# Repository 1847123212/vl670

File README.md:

VL670/VL671 Development Board - USB 2.0 to 3.0 Transaction Translator
======================================================================

### Revision

This is version v0.02b (git branch usb-b), which removes the USB Type-C
connector due to chip shortage.

The v0.02 design with the original USB Type-C connector is
[here](https://notabug.org/niconiconi/vl670/src/main)

The original v0.01 design is obsolete, but it's still
[available here](https://notabug.org/niconiconi/vl670/src/v0.01).

### Introduction

#### The Problem

From a technical standpoint, USB 3.0 SuperSpeed (5 Gbps) is not an
upgrade to the existing USB 2.0 High-Speed (480 Mbps) standard,
instead, USB 3.0 is a completely new system of its own, which
operates independently from USB 2.0. Both the physical and protocol
layer have major differences. Backward compatibility is only maintained
by mandating all USB 3.0 devices to include a separate set of legacy
USB 2.0 controllers, transceivers, and wirings.

Because a USB 3.0 port is really a USB 3.0 and USB 2.0 port slapped
together, it creates some limitations.

* Bandwidth: You may want to simutaneously access multiple USB 2.0
devices, such as many USB flash drives, video cameras, or Software
Defined Radios (SDR) over a single USB 3.0 port using a USB hub,
since it has 5 Gbps bandwidth. However, you cannot do this - the total
bandwidth of all USB 2.0 devices is still limited to 480 Mbps, just
like a regular USB 2.0 port.

* Signal Extension and Isolation: Counter-intuitively, it's easier to
transmit USB 3.0 signals (not USB 2.0 High-Speed) over long distances,
or to galvanically isolate them. Its physical layer is actually simpler
than USB 2.0 - it uses two pairs of unidirectional, 8b/10b encoded,
differential signals. This type of signal is commonly found in almost
all high-speed digital systems, many standard hardware interfaces and
transceivers exist. On the other hand, USB 2.0 signaling is its own
design, its half-duplex nature further complicates the implementation.
Thus, in some non-standard custom systems, only a USB 3.0 link is
physically available.

For home and office users, both limitations may not be a problem,
but for hardware developers and experimenters who work with custom
systems, this can be problematic.

#### VL670/VL671 Transaction Translator

The VL670/671 is a specialized ASIC developed by VIA Labs, Inc., it's a USB
2.0 to USB 3.0 *transaction translator*, in other words, it translates the
legacy USB 2.0 traffic and transparently upgrades the device to an USB 3.0
SuperSpeed device by emulation, enabling a legacy USB 2.0 device to make use
of USB 3.0. By transparently upgrading a legacy USB 2.0 device to an emulated
USB 3.0 device, both problems are eliminated.

This is not a perfect solution, first, it's technically a violation of the
USB standards, also device compatibility is limited. Nevertheless, it's
still helpful to hardware developers and can solve many practical problems
in hardware Research and Development.

This technology is marketed as "SuperTT" (Super Transaction Translator)
by some OEM vendors.

#### My Project

Due to the specialized nature of the VL670/VL671 ASIC, it's almost unheard of
by most developers.

This project is an effort to create a free and open source hardware design of a
development board for the VL670/VL671 ASIC, to facilitate hardware evaluation and
experiments by other community developers, hopefully to help solving your USB
problems in your custom systems.

This development board is intended solely for hardware or software developers for
use in a research and development setting to facilitate evaluation, experimentation,
or technical analysis. It's not designed for consumer use, and it also should not be
used as a part or subassembly in any finished product.

#### Generations

VL670 is already obsolete. The second generation is VL671. This development board
supports both VL670 and VL671, and the use of VL671 is strongly recommended (though
not without its own problems).

Both chips are highly compatibile, the only modification needed is a single LED
output.  If VL670 is used, solder resistor `R9`, otherwise, solder resistor `R13`.

### Usage

#### LED Status

##### D2

* On: A USB 2.0 device has just connected and its traffic is being translated
to USB 3.0 traffic by VL67x (*VL670 only, not on VL671: or the processor is being
held in reset by the SPI header*).

* Off: A USB 3.0 or 2.0 device is connected and its traffic is passing
through VL670 as-is without any translation.

* Blink: Initial power-on reset, or a USB 2.0 device has just connected (*VL670
only, not on VL671*).

##### D20

* On: The power rail `+5V_SW` for downstream USB-A port is switched on.
Normally, this LED should be always on.

* Off: The power rail `+5V_SW` for downstream USB-A port is switched off.
This indicates the power supply circuit is malfunctional. First, check the
`5V` input, and whether the downstream USB port has a short circuit. Then,
check the USB power switch chip `U4` and pull-down resistor R15.

#### Voltage Level

All I/O are 3.3 V LVCMOS. Applying 5 V TTL level can damage the VL670,
its SPI flash, or both.

Before reading or writing to the Flash via SPI, the 5V power must also be
applied via the USB cable or the pin header. Attempting to program the SPI
Flash with an external programming without applying 5V power can damage
components.

#### SPI header

An SPI pin header is located at the top right of the board. By default, it's
connected directly to both the VL670 controller and its SPI Flash, allowing
one to probe the SPI bus while the controller is running. In this default mode,
applying voltages to the SPI header is prohibited, otherwise damage may occur.

To read or write the Flash via SPI, the `/EN` (a.k.a `ISP_ENABLE`) pin of the pin
header is grounded (by bridging pin 6 and 7 on the pin header), the processor is
cut off from the SPI bus and held in reset, giving the SPI pin header exclusive
access to the Flash.

For more information, see *Theory of Operation*, section *SPI Debugging and
Programming* and schematics.

#### GPIO header

All GPIO pin header is located at the top left of the board, exposing all
GPIOs of VL67x. Nevertheless, their functionality is unclear and it's
only useful for reverse engineering.

For more information, see *Theory of Operation*, section *Oddities* and
schematics.

### Known Issues

#### Limitations

1. If the USB-C cable is inserted very slowly, USB 3.0 fails, only USB 2.0
is detected, thus forcing the chip to enter USB 2.0 passthrough mode. This
is working by design and it's not a bug, however, it may cause misleading
or confusing behaviors, thus, `R1` and `R2` are removed by default, forcing
VL67x to always work in transaction translator mode.

2. In VL670, USB 3.0 passthrough is not reliable and it's not compatible
with some devices, this is a VL670 limitation. In VL671, USB 3.0 passthrough
is almost completely broken due to firmware limitation, the only compatible
device is a USB 3 Hub, direct attachment of a USB 3 device is not compatible.
Also, because the USB 3 signal path is doubled in passthrough mode, any cable
longer than 50 centimeters may cause enumeration failures. Thus, USB 3.0
passthrough mode should be avoided. If you want to test a combo USB 2/3 device,
I recommend using a pure USB 2.0 hub to completely isolate the USB 3 signals.

    * If you ever need to test USB 3.0 passthrough mode, you should always
    use a short USB-C cable, no longer than 50 centimeters to minimize signal
    loss. The ideal setup for USB 3 passthrough testing is: Host, 50 centimeter
    USB cable, VL671, very short USB cable, USB 3 Hub, device. Failure to follow
    it to cause enumeration and other failures. For USB 2 transaction mode, no
    special precaution is needed.

    * A hybrid VL670 w/ USB hub topology can be used to work around the
    problem, it's briefly in the next section of the document. USB redrivers
    and retimers can also solve the hardware problem (but not the firmware
    bug). Since USB 3 passthrough is already broken enough and adding either
    solution makes the project more complicated, I choose not to do it.

3. The upstream and downstream USB ports have no common-mode chokes for
the signals. Electromagnetic compatibility performance is limited. This
is an intentional decision, since adding them reduces the USB 3 link
budget needed for the already problematic USB 3 passthrough mode.

4. Not all devices are supported by the transaction translator. Sometimes
the incompatibility is a hardware or protocol limitation, other times it
can be a driver problem - many drivers make certain assumptions of the USB
device, which may no longer be true after the device is emulated by VL670
as a SuperSpeed device.

    * USB Attached SCSI (UAS) doesn't work in transaction translator mode.
    But it can be disabled at the device driver of the operating system.

### Photos

#### Front and Back of the PCB

### Schematics

* [PDF schematics](https://notabug.org/niconiconi/vl670/raw/usb-b/schematics/vl670-schematics.pdf)

* [PDF layout](https://notabug.org/niconiconi/vl670/raw/usb-b/schematics/vl670-layout.pdf)

### BOM

* [Bill of Material](https://notabug.org/niconiconi/vl670/src/usb-b/bom)

### Datasheets

Datasheets for all components on the development board can be found at GitLab.

* [Datasheets Repository](https://gitlab.com/niconicon1/vl670-datasheets)

It contains the following documents.

* [VL670 USB2.0 to USB3.0 Transaction Translator](https://gitlab.com/niconicon1/vl670-datasheets/-/raw/main/DS_VL670_115.pdf)

* [VL671 Low Power USB 2.0 to USB 3.1 Gen1 Transaction Translator](https://gitlab.com/niconicon1/vl670-datasheets/-/raw/main/DS_VL671_080.PDF)

* [HD3SS3220 USB Type-C DRP Port Controller with SuperSpeed 2:1 MUX](https://gitlab.com/niconicon1/vl670-datasheets/-/raw/main/hd3ss3220.pdf)

* [TPS20xxC and TPS20xxC-2 Current Limited, Power-Distribution Switches](https://gitlab.com/niconicon1/vl670-datasheets/-/raw/main/tps2061c.pdf)

* [GD25D10C/05C 3.3V Uniform Sector Standard and Dual Serial Flash](https://gitlab.com/niconicon1/vl670-datasheets/-/raw/main/GD25D05C.pdf)

* [SN74LVC2G66 Dual Bilateral Analog Switch](https://gitlab.com/niconicon1/vl670-datasheets/-/raw/main/sn74lvc2g66.pdf)

* [ESD7104 Low Capacitance ESD Protection Diode for High Speed Data Line](https://gitlab.com/niconicon1/vl670-datasheets/-/raw/main/ESD7104-D.PDF)

* [ESD5B5.0ST1G-N ESD Protection Diode](https://gitlab.com/niconicon1/vl670-datasheets/-/raw/main/ESD5B5.0ST1G-N.pdf)

### Firmware

The firmware for the SPI Flash can be found at GitLab. Both VL670 and VL671
firmware files are included.

* [SPI Flash Firmware](https://gitlab.com/niconicon1/vl670-firmware)

#### Non-Free

Unfortunately, VL670/671 is driven by a microcontroller and requires a
proprietary firmware to operate.

Nevertheless, the firmware is burned into the Flash memory only once after
the device is assembled, and it's fetched by the VL670 ASIC itself, not
uploaded from a user's host computer, nor it executes any code on a user's
host computer or operating system. If we make the firmware read-only and
unmodifiable by pure software, the firmware effectively "vanishes" from the
software domain and becomes a part of the hardware itself, making the hardware
qualifies as free device, just like [how OpenMoko did it](https://lwn.net/Articles/460654/).
Another benefit is improved security, as malicious software is unable to
reprogram the firmware via USB to launch a BadUSB attack.

This is implemented as jumper `JP1`, once the jumper is hardwired on the board,
the Flash is read-only and cannot be modified by software without hardware
modifications.

That being said, this is a somewhat "underhanded" way to bypass the free software
and hardware requirements and this behavior stays exactly at the borderline of
the definition of "free", just moving one more nanometer away makes it non-free.
This is hardly satisfactory! But this is all we have at the current moment.

#### Reverse Engineering

The long term solution is reverse engineering the firmware and writing a free and
open reimplementation. This also enables us to customize the firmware for our
needs, fixing bugs in the firmware, and understanding the behavior of the hardware
better.

But before you start, note that VL670 is already obsolete, its internal
microcontroller uses an Xtensa core. Its replacement, VL671, uses a different
core (ARM Cortex M3) and a different firmware.

I suggest leaving the proprietary VL670 firmware as-is since its architecture
is less known and the chip is already obsolete. Instead, work on the VL671
firmware instead.

### Theory of Operation

#### Overview

The heart of the development board is the VL67x controller (`U2`). It has two USB
interfaces on both sides of the chip. The left side is the host side, connnected
to a computer via a USB 3.0 Type-B port (`J2`), the right side is connected to
the device side, via a USB 3.0 Type-A port. All the transaction translation
magic is performed internally by VL67x.

When a USB Type-B cable is plugged into the development board, 5 V power is
applied to the board by the host, the decoupling capacitors on the 5 V rail
starts charging up. Shortly after the 5 V rail settles, the internal power
converters inside the VL67x controller (`U2`) are activated. They are a 3.3 V
LDO, a 1.5 V DC/DC, and a 1.2 V LDO converter, generating the three power rails
for VL670 (on VL671, the 1.5 V & 1.2 V is merged into a single 1.2 V DC/DC
converter), the SPI Flash (`U6`), and the SPI multiplexers (`U3` and `U5`).

When 3.3 V is ready, the VL67x controller (`U2`) leaves the power-on reset
state, timed by the RC circuit `R4` and `C13`, and the processor core inside
VL67x starts operating. VL67x fetches firmware code from the Flash chip GD25D05
(`U6`) via the SPI bus.

At this point, VL67x gains access to both USB 3.0 and USB 2.0 signals at the
host side, from the USB Type-B connector.

Strictly speaking, only the USB 3.0 signals are required since VL67x is a
transaction translator that converts all USB 2.0 traffic to USB 3.0 transparently.
The USB 2.0 differential pair at the host side is only for compatibility -
if one plugs the board into a USB 2.0 port, VL67x disables transaction and enters
USB 2.0 passthrough mode. Because this fallback behavior can confuse the developer
(e.g. for example, if the USB 3.0 cable is defective and the chip always enters
USB 2.0 passthrough mode), optional jumpers, `R1` and `R2`, are installed on the
the USB 2.0 signal lines. USB 2.0 is disconnected completely when the resistors
are removed to simulate a nonstandard, pure USB 3.0 host port without USB 2.0
connection.

Once the firmware in VL67x decides that it's ready, `/DN_PWREN` (pin 37) outputs
a logical `0`, enabling power switch TPS2061C (`U4`) to provide 5 V power (called
`+5V_SW`, for "switched 5 V") to the downstream, device-side USB port (`J4`).
TPS2061C also provides soft-start and short-circuit protection. At this point,
VL67x is ready to accept a USB device.

At the device side, `DN_D-`, `DN_D+`, `DN_USB3RX-`, `DN_USB3RX+`, `DN_USB3TX-`,
`DN_USB3TX+` are connected to a USB Type-A port.

When a USB device is plugged in to the USB-A connector (`J4`)...

* If it's a USB 2.0 device and if USB 3.0 is available at the host side, the
USB 2.0 traffic is translated to USB 3.0 traffic by VL67x. The host should
detect a USB 3.0 SuperSpeed device. The translation is transparent, VL67x
itself is invisible to the host, only the device is.

* If only USB 2.0 is available at the host, VL67x enters USB 2.0 passthrough
mode for all USB 2.0 or USB 3.0 devices, without translation. The host should
detect a USB 2.0 device. This mode is also entered if the USB 3.0 at the host
side has failed. A defective cable is a common cause, but inserting the USB
cable extremely slowly has the same effect. Removing `R1` and `R2` to disable
USB 2.0 at the host completely can avoid this confusing situation.

* If both the host and device support USB 3.0, VL67x enters passthrough mode
without translation.

#### SPI Debugging and Programming

An SPI pin header (`J3`) is provided at the top right of the board. The header is
directly connected to the signal lines between the VL67x controller and the
GD25D05 (`U6`) SPI Flash, allowing one to attach a logic analyzer to monitor the
bus while the controller is running.

To allow a developer to read or write the Flash via SPI directly without a
potentially destructive bus contention, VL67x's SPI bus is gated by two
74LVC2G66 CMOS analog switches (`U3` and `U5`). When the `/EN` (a.k.a `ISP_ENABLE`)
pin of the pin header is grounded (by bridging pin 6 and 7 on the pin header),
the processor is cut off from the SPI bus, giving the SPI pin header exclusive
access to the Flash. The `/EN` signal is also directly connected to the `/RESET`
signal of VL67x to halt the processor.

#### External Power

A power pin header (`J5`) is provided. However, it should never be used to power
the development board when the USB Type-B port is plugged in, otherwise a short
circuit may occur. If debugging the board with external power is desirable, cut
the trace at PCB jumper `JP2` with a knife.

The jumper is located at the back side of the board. There are two jumpers, so
make sure you're cutting `JP2`. Use a multimeter to confirm the connection is
truly broken.

Once `JP2` is cut, the USB Type-B port no longer provides power to the
development board. Signals and ground connections remain.

#### Oddities

Due to OEM firmware differences, some pins do different things than what
they were intended to do. These differences were obtained via hardware
reverse engineering.

##### GPIO

* `GPIO1_3 / DN_PWREN` is meant to be an `/ENABLE` signal to the downstream
USB port, but it seems to be high-impedance and unused by the firmware. Thus,
the USB power switch U2 is optional and can be removed. Its only purpose is
short circuit protection.

##### USB 3 Passthrough

The reverse-engineered hardware uses a slightly different topology -
VL67x is attached to an upstream USB 3.0 hub as a subdevice, and only
USB 2.0 signals are wired to the downstream VL670, the USB 3.0 signals
are directly wired to the upstream hub. This can be understood as an
attempt to improve compatibility. In my tests, I found the USB 3.0
passthrough offered by VL670 is not always reliable and some devices
cannot be used, and on VL671 it's essentially broken due to firmware
limitations. Furthur, because the USB 3 signal path is doubled in
passthrough mode, it completely breaks the USB link budget, any cable
longer than 50 centimeters may cause enumeration failures.

Thus, passthrough mode should be avoided. Wiring the USB 3.0 signal
directly to the host via a USB 3.0 hub is beneficial.

For simplicity, this is not implemented on this development board. But
it's necessary for a finished product.

##### VL670 GPIO

* `GPIO1_2 / GPIO_TP3` is officially unused, but the OEM firmware uses it as
an input for deciding whether to enable VL670. On this development board, this
pin is pulled down by a resistor, otherwise the USB connection would reset
randomly.

On the reverse-engineered hardware, the downstream hub `/ENABLE` seems to
be Wired-Or together with `DN_PWREN` output, the `ENABLE` pin output from
the upstream USB Hub (to allow both chips to make a `ENABLE` decision?),
and the input `GPIO1_2`. It appears to be a workaround to allow the use
of aforementioned hybrid topology.

* `GPIO1_0 / GPIO_TP1` is officially unused, but the OEM hardware connects it
to the USB hub's (not VL670's own) private SPI bus, between the hub and its SPI
firmware Flash, monitoring the `MISO` signal. On this development board, this
pin is pulled down by a resistor. Although it seems to work without one, but
leaving the input in a known state is still desirable as we don't really
understand its purpose.

Again, a odd design, and I suspect the firmware is using it as an interrupt
signal to detect whether the USB hub is active for logic sequencing or
synchronization in this hybrid VL670 w/ hub topology.

* `GPIO3_0 / STATUS` is meant to be the LED indicator output, but the
firmware uses `GPIO1_1/GPIO_TP2` instead.

* `UART_RX` and `UART_TX` - no traffic observed. More hacking required.

#### Power Distribution Network

##### Overview

The Power Distribution Network is decoupled using the standard method of
"one capacitor per pin, all capacitors have the same value."

The 1.5 V rail and 1.2 V rail are decoupled using 1 uF capacitors, all
0603-sized, nothing unusual (but do note C44 is the output capacitor of
the DC/DC converter).

The 3.3 V rail uses multiple (20+) 470 nF capacitors and deserves more
attention: C31-C35 are meant for power supply decoupling, and are 0603-sized.
C71-C82 however, serve double duties, they are placed near vias to provide a
continuous AC return path for signals travelling between layers ("plane
stitching"), thus are 0402-sized to fit in the tight space near vias. Due to
the higher number of capacitors for plane stitching, smaller 470 nF capacitors
are used to keep the total capacitance per rail under 10 uF to prevent inrush
current.

##### USB Inrush Current

The 5 V rail requires special care, it's directly attached to the USB power
input, thus will produce a huge inrush current, which should stay within the
USB spec limits. Basically, the rules of the USB spec is:

1. Inrush current less than 100 mA is always acceptable, it's only considered
as an inrush event when 100 mA is exceeded.

2. If an inrush event occurs, the maximal *charge* transfered, calculating by
area under the current curve, should be less than 50 uC. For 5 V, it means the
equivalent capacitance should be less than 10 uF. Only *charge* is limited, not
inrush current itself, because the goal is to avoid draining the output
capacitance at the upstream by too much, the absolute current is irrelevant (of
course, unless it's low enough to apply rule No.1).

3. If two inrush events are separated by 100+ us, they are considered as two
separate events. Only the "biggest" inrush event is considered, all other
events are ignored. Thus, it's possible to get more capacitance allowance
by delayed startup.

Measurements showed that the only significant inrush current of this development
board is caused by capacitors at 5 V rail, other power rails produces almost no
inrush current, presumably, the LDO and DC/DC's startup is "soft" enough.
Moreover, the current capacitance on 5 V rail is rather conservative, only 5 uF,
due to the delayed (100 us+) startup of `+5V_SW` rail, the total capacitance
allowed on the +5 V rail is effectively doubled, up to 20 uF (effectively 10 uF
due to ceramic capacitance loss under DC bias, giving us some extra headroom).

##### Ferrite Resonance and Damping

A ferrite choke, FB1, is used in series of the 5 V input at the USB port to
filter high-frequency noise. However, its series inductance, when combined
with parallel capacitance, forms a parallel LC circuit on the 5V rail. This
creates a huge impedance spike at the resonance frequency. If this frequency
is excited by noise, it create a huge noise voltage. To reduce its impact,
two small 0.5-ohm resistors are connected in series with the ceramic capacitors,
C19 and C20.

##### Capacitor Value Selection

Finally, it should be noted that a 0.1 uF capacitor is traditionally seen as
a "high-frequency capacitor" and is the prefered choice for power decoupling,
and is often blindly combined with 1 uF capacitors to "cover both high and
low frequencies." However, many recent books by domain experts have pointed out
that this practice is counterproductive. First, blindly mixing capacitor
values can create anti-resonance impedance peaks and actually make the
decoupling worse at some frequencies. Second, considering that this rule of
thumb originated from the through-hole era, meanwhile the parasitic inductance
of modern SMD ceramic capacitors is so low, they all have fairly good
high-frequency performance regardless of their values, their effectiveness is
mainly limited by package size and PCB inductance. Thus, the modern, updated
guideline is to use the same capacitance everythere. That being said, there
are still important uses and benefits for mixing different capacitance, but
only if careful calculation and simulation is performed to predict and control
the anti-resonance peaks - which is overkill for this board.

For the argument against multiple capacitor values, see *Electromagnetic
Compatibility Engineering* by Henry Ott, Chapter 11 *Digital Circuit Power
Distribution*, Section 11.4.1 *Multiple Decoupling Capacitors*. And for the
argument for multiple capacitor values, but with careful design and simulation,
see *Principles of Power Integrity for PDN Design* by Larry D. Smith and Eric
Bogatin, Chapter 8 *The PDN Ecology*, Section 8.17 *Using Three Different
Values of MLCC Capacitors on the Board*.

P.S: Smith & Bogatin's conclusions are terrifying, I'll just pretend that I
don't know that...

#### PCB Stack-up

This is a 4-layer PCB, using the Signal-Ground-Power-Signal stack-up
with impedance controlled traces, and fabricated by JLCPCB's JLC2313
stack-up. The dielectric constant of the board is 4.05, the distance
between the signal and its reference plane is 0.1 mm.

JLC2313 is selected for its closer distance between the signal and its
reference plane in comparison to JLC7628, which allows thinner traces
and reduced crosstalk.

### License

Copyright (C) 2021 Tom Li (niconiconi)
"No Rights Reserved"

This is a free hardware design: to the extent possible under law, the designer
has waived all copyright and related or neighboring rights, you can reuse,
modify, redistribute this design, as freely as possible in any form whatsoever
and for any purposes, including commercial purposes, under the terms of the
*CC0 1.0 Universal License*.

This hardware design is offered as-is and the designer makes no representations
or warranties of any kind concerning the design, express, implied, statutory or
otherwise, including without limitation warranties of title, merchantability,
fitness for a particular purpose, non infringement, or the absence of latent
or other defects, accuracy, or the present or absence of errors, whether or
not discoverable, all to the greatest extent permissible under applicable law.

See the *CC0 1.0 Universal License* for more details.

You should have received a copy of the *CC0 1.0 Universal License* along with
this hardware design. If not, see https://creativecommons.org/publicdomain/zero/1.0/legalcode

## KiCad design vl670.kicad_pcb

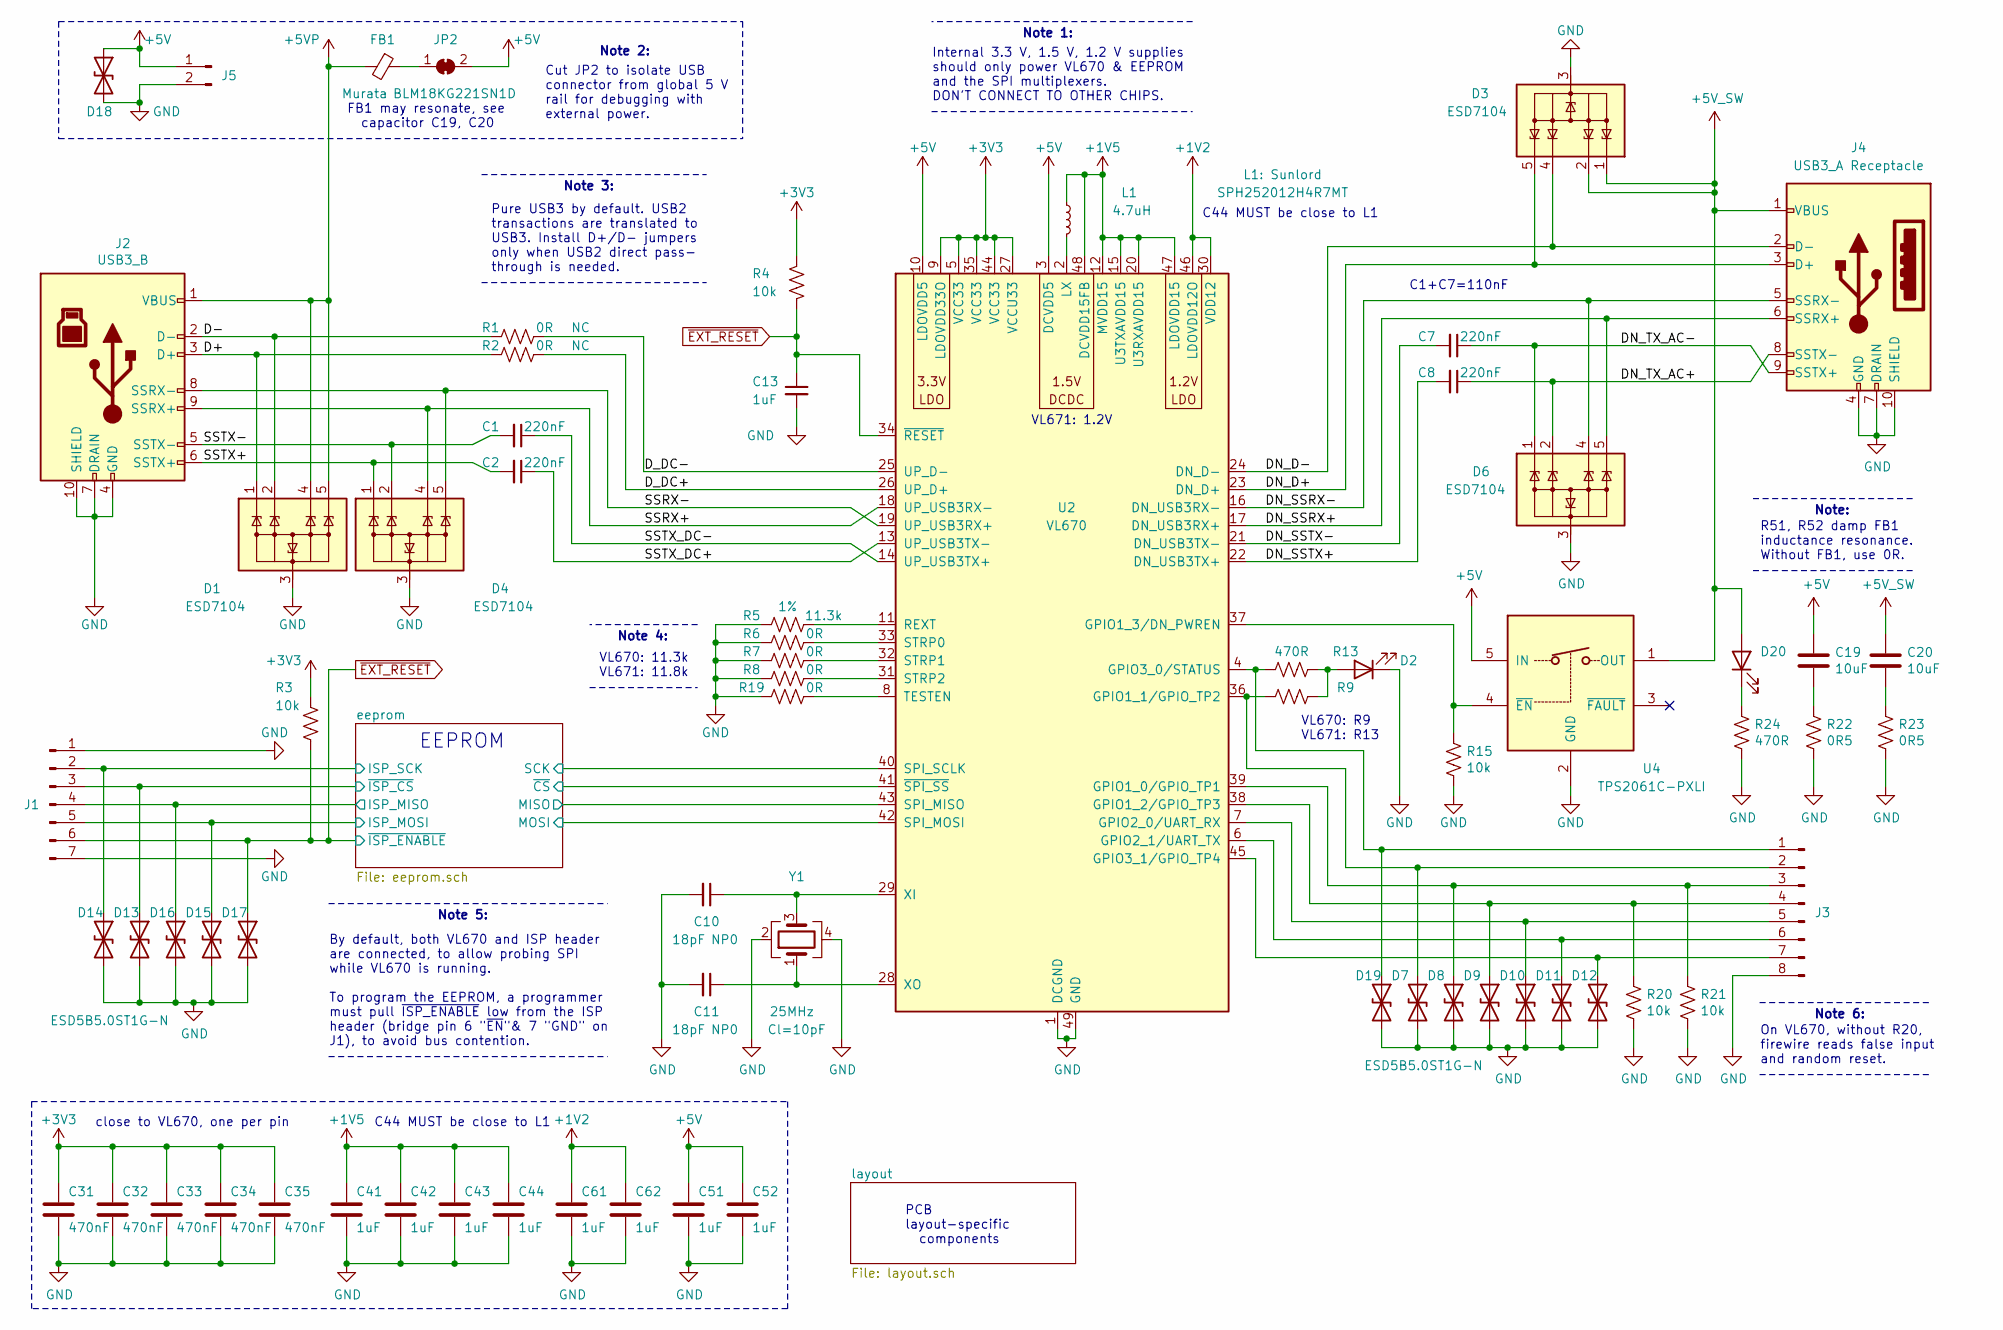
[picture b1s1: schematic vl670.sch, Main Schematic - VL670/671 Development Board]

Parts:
C1, C2, C7, C8: 220nF; C_0603_1608Metric_Pad1.08x0.95mm_HandSolder
C10, C11: 18pF; C_0603_1608Metric_Pad1.08x0.95mm_HandSolder
C13, C41, C42, C43, C44, C51, C52, C61, C62: 1uF; C_0603_1608Metric_Pad1.08x0.95mm_HandSolder
C19, C20: 10uF; C_0603_1608Metric_Pad1.08x0.95mm_HandSolder
C31, C32, C33, C34, C35: 470nF; C_0603_1608Metric_Pad1.08x0.95mm_HandSolder
D1, D3, D4, D6: ESD7104; OnSemi_UDFN-10_1.0x2.5mm_P0.5mm
D2, D20: LED; LED_0603_1608Metric_Pad1.05x0.95mm_HandSolder
D7, D8, D9, D10, D11, D12, D13, D14, D15, D16, D17, D19: ESD5B5.0ST1G-N; D_SOD-523
D18: ESD7951S; D_SOD-523
FB1: BLM18KG221SN1D; L_0603_1608Metric_Pad1.05x0.95mm_HandSolder
J1: Conn_01x07_Male; PinHeader_1x07_P2.54mm_Vertical
J2: USB3_B; USB3_B_XKB_U235-091N-4BLRC16-4-5
J3: Conn_01x08_Male; PinHeader_1x08_P2.54mm_Vertical
J4: USB3_A Receptacle; USB3_A_Receptacle_XKB_U231-091N-4BLRA00-S-1
J5: Conn_01x02_Male; PinHeader_1x02_P2.54mm_Vertical
JP2: SolderJumper_2_Bridged; SolderJumper-2_P1.3mm_Bridged_RoundedPad1.0x1.5mm
L1: 4.7uH; L_1008_2520Metric_Pad1.43x2.20mm_HandSolder; Part Number SPH252012H4R7MT
R1, R2, R6, R7, R8, R19: 0R; R_0603_1608Metric_Pad0.98x0.95mm_HandSolder
R3, R4, R15, R20, R21: 10k; R_0603_1608Metric_Pad0.98x0.95mm_HandSolder
R5: 11.3k; R_0603_1608Metric_Pad0.98x0.95mm_HandSolder; Tolerance 1%
R9, R13, R24: 470R; R_0603_1608Metric_Pad0.98x0.95mm_HandSolder
R22, R23: 0R5; R_0603_1608Metric_Pad0.98x0.95mm_HandSolder
U2: VL670; QFN-48-1EP_6x6mm_P0.4mm_EP4.3x4.3mm
U4: TPS2061C-PXLI; SOT-23-5_HandSoldering
Y1: 25MHz; Crystal_SMD_3225-4Pin_3.2x2.5mm

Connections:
+1V2: C61.1, C62.1, U2.30 (VDD12), U2.46 (LDOVDD12O); also elsewhere on the board
+1V5: C41.1, C42.1, C43.1, C44.1, L1.1, U2.12 (MVDD15), U2.15 (U3TXAVDD15), U2.20 (U3RXAVDD15), U2.47 (LDOVDD15), U2.48 (DCVDD15FB); also elsewhere on the board
+3V3: C31.1, C32.1, C33.1, C34.1, C35.1, R3.1, R4.1, U2.5 (VCC33), U2.9 (LDOVDD33O), U2.27 (VCCU33), U2.35 (VCC33), U2.44 (VCC33); also elsewhere on the board
+5V: C19.1, C51.1, C52.1, D18.1 (A1), J5.1, JP2.2 (B), U2.3 (DCVDD5), U2.10 (LDOVDD5), U4.5 (IN)
+5VP: D1.4 (TVS3), D1.5 (TVS4), D1.6 (NC4), D1.7 (NC3), FB1.2, J2.1 (VBUS)
+5V_SW: C20.1, D3.1 (TVS1), D3.2 (TVS2), D3.9 (NC2), D3.10 (NC1), D20.2 (A), J4.1 (VBUS), U4.1 (OUT)
/D+: D1.1 (TVS1), D1.10 (NC1), J2.3 (D+), R2.2
/D-: D1.2 (TVS2), D1.9 (NC2), J2.2 (D-), R1.2
/DN_D+: D3.5 (TVS4), D3.6 (NC4), J4.3 (D+), U2.23 (DN_D+)
/DN_D-: D3.4 (TVS3), D3.7 (NC3), J4.2 (D-), U2.24 (DN_D-)
/DN_SSRX+: D6.5 (TVS4), D6.6 (NC4), J4.6 (SSRX+), U2.17 (DN_USB3RX+)
/DN_SSRX-: D6.4 (TVS3), D6.7 (NC3), J4.5 (SSRX-), U2.16 (DN_USB3RX-)
/DN_SSTX+: C8.2, U2.22 (DN_USB3TX+)
/DN_SSTX-: C7.2, U2.21 (DN_USB3TX-)
/DN_TX_AC+: C8.1, D6.2 (TVS2), D6.9 (NC2), J4.8 (SSTX-)
/DN_TX_AC-: C7.1, D6.1 (TVS1), D6.10 (NC1), J4.9 (SSTX+)
/D_DC+: R2.1, U2.26 (UP_D+)
/D_DC-: R1.1, U2.25 (UP_D-)
/SSRX+: D4.4 (TVS3), D4.7 (NC3), J2.9 (SSRX+), U2.18 (UP_USB3RX-)
/SSRX-: D4.5 (TVS4), D4.6 (NC4), J2.8 (SSRX-), U2.19 (UP_USB3RX+)
/SSTX+: C2.2, D4.1 (TVS1), D4.10 (NC1), J2.6 (SSTX+)
/SSTX-: C1.2, D4.2 (TVS2), D4.9 (NC2), J2.5 (SSTX-)
/SSTX_DC+: C2.1, U2.13 (UP_USB3TX-)
/SSTX_DC-: C1.1, U2.14 (UP_USB3TX+)
/eeprom/ISP_MISO: D16.1 (A1), J1.4; also elsewhere on the board
/eeprom/ISP_MOSI: D15.1 (A1), J1.5; also elsewhere on the board
/eeprom/ISP_SCK: D14.1 (A1), J1.2; also elsewhere on the board
/eeprom/MISO: U2.43 (SPI_MISO); also elsewhere on the board
/eeprom/MOSI: U2.42 (SPI_MOSI); also elsewhere on the board
/eeprom/SCK: U2.40 (SPI_SCLK); also elsewhere on the board
/eeprom/~CS: U2.41 (~SPI_SS); also elsewhere on the board
/eeprom/~ISP_CS: D13.1 (A1), J1.3; also elsewhere on the board
GND: C10.2, C11.2, C13.2, C31.2, C32.2, C33.2, C34.2, C35.2, C41.2, C42.2, C43.2, C44.2, C51.2, C52.2, C61.2, C62.2, D1.3 (COM), D1.8 (GND), D2.1 (K), D3.3 (COM), D3.8 (GND), D4.3 (COM), D4.8 (GND), D6.3 (COM), D6.8 (GND), D7.2 (A2), D8.2 (A2), D9.2 (A2), D10.2 (A2), D11.2 (A2), D12.2 (A2), D13.2 (A2), D14.2 (A2), D15.2 (A2), D16.2 (A2), D17.2 (A2), D18.2 (A2), D19.2 (A2), J1.1, J1.7, J2.4 (GND), J2.7 (DRAIN), J2.10 (SHIELD), J3.8, J4.4 (GND), J4.7 (DRAIN), J4.10 (SHIELD), J5.2, R5.2, R6.2, R7.2, R8.2, R15.2, R19.2, R20.2, R21.2, R22.2, R23.2, R24.2, U2.1 (DCGND), U2.49 (GND), U4.2 (GND), Y1.2, Y1.4; also elsewhere on the board
unnamed: C10.1, U2.29 (XI), Y1.3
unnamed: C11.1, U2.28 (XO), Y1.1
unnamed: C19.2, R22.1
unnamed: C20.2, R23.1
unnamed: D2.2 (A), R9.1, R13.1
unnamed: D7.1 (A1), J3.2, R9.2, U2.36 (GPIO1_1/GPIO_TP2)
unnamed: D8.1 (A1), J3.3, R21.1, U2.39 (GPIO1_0/GPIO_TP1)
unnamed: D9.1 (A1), J3.4, R20.1, U2.38 (GPIO1_2/GPIO_TP3)
unnamed: D10.1 (A1), J3.5, U2.7 (GPIO2_0/UART_RX)
unnamed: D11.1 (A1), J3.6, U2.6 (GPIO2_1/UART_TX)
unnamed: D12.1 (A1), J3.7, U2.45 (GPIO3_1/GPIO_TP4)
unnamed: D19.1 (A1), J3.1, R13.2, U2.4 (GPIO3_0/STATUS)
unnamed: D20.1 (K), R24.1
unnamed: FB1.1, JP2.1 (A)
unnamed: L1.2, U2.2 (LX)
unnamed: R5.1, U2.11 (REXT)
unnamed: R6.1, U2.33 (STRP0)
unnamed: R7.1, U2.32 (STRP1)
unnamed: R8.1, U2.31 (STRP2)
unnamed: R15.1, U2.37 (GPIO1_3/DN_PWREN), U4.4 (~EN)
unnamed: R19.1, U2.8 (TESTEN)
~EXT_RESET: C13.1, D17.1 (A1), J1.6, R3.2, R4.2, U2.34 (~RESET~); also elsewhere on the board

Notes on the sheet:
Note 1:
Note 4:
Pure USB3 by default. USB2 transactions are translated to USB3. Install D+/D- jumpers only when USB2 direct pass- through is needed.
Note 3:
EEPROM
Note 5:
By default, both VL670 and ISP header are connected, to allow probing SPI while VL670 is running. To program the EEPROM, a programmer must pull ~ISP_ENABLE~ low from the ISP header (bridge pin 6 "~EN~"& 7 "GND" on J1), to avoid bus contention.
C44 MUST be close to L1
close to VL670, one per pin
On VL670, without R20, firewire reads false input and random reset.
Note 6:
Internal 3.3 V, 1.5 V, 1.2 V supplies should only power VL670 & EEPROM and the SPI multiplexers. DON'T CONNECT TO OTHER CHIPS.
VL670: 11.3k VL671: 11.8k
Note 2:
Cut JP2 to isolate USB connector from global 5 V rail for debugging with external power.
R51, R52 damp FB1 inductance resonance. Without FB1, use 0R.
PCB layout-specific components
FB1 may resonate, see capacitor C19, C20
Note:
C1+C7=110nF
VL671: 1.2V
VL670: R9 VL671: R13

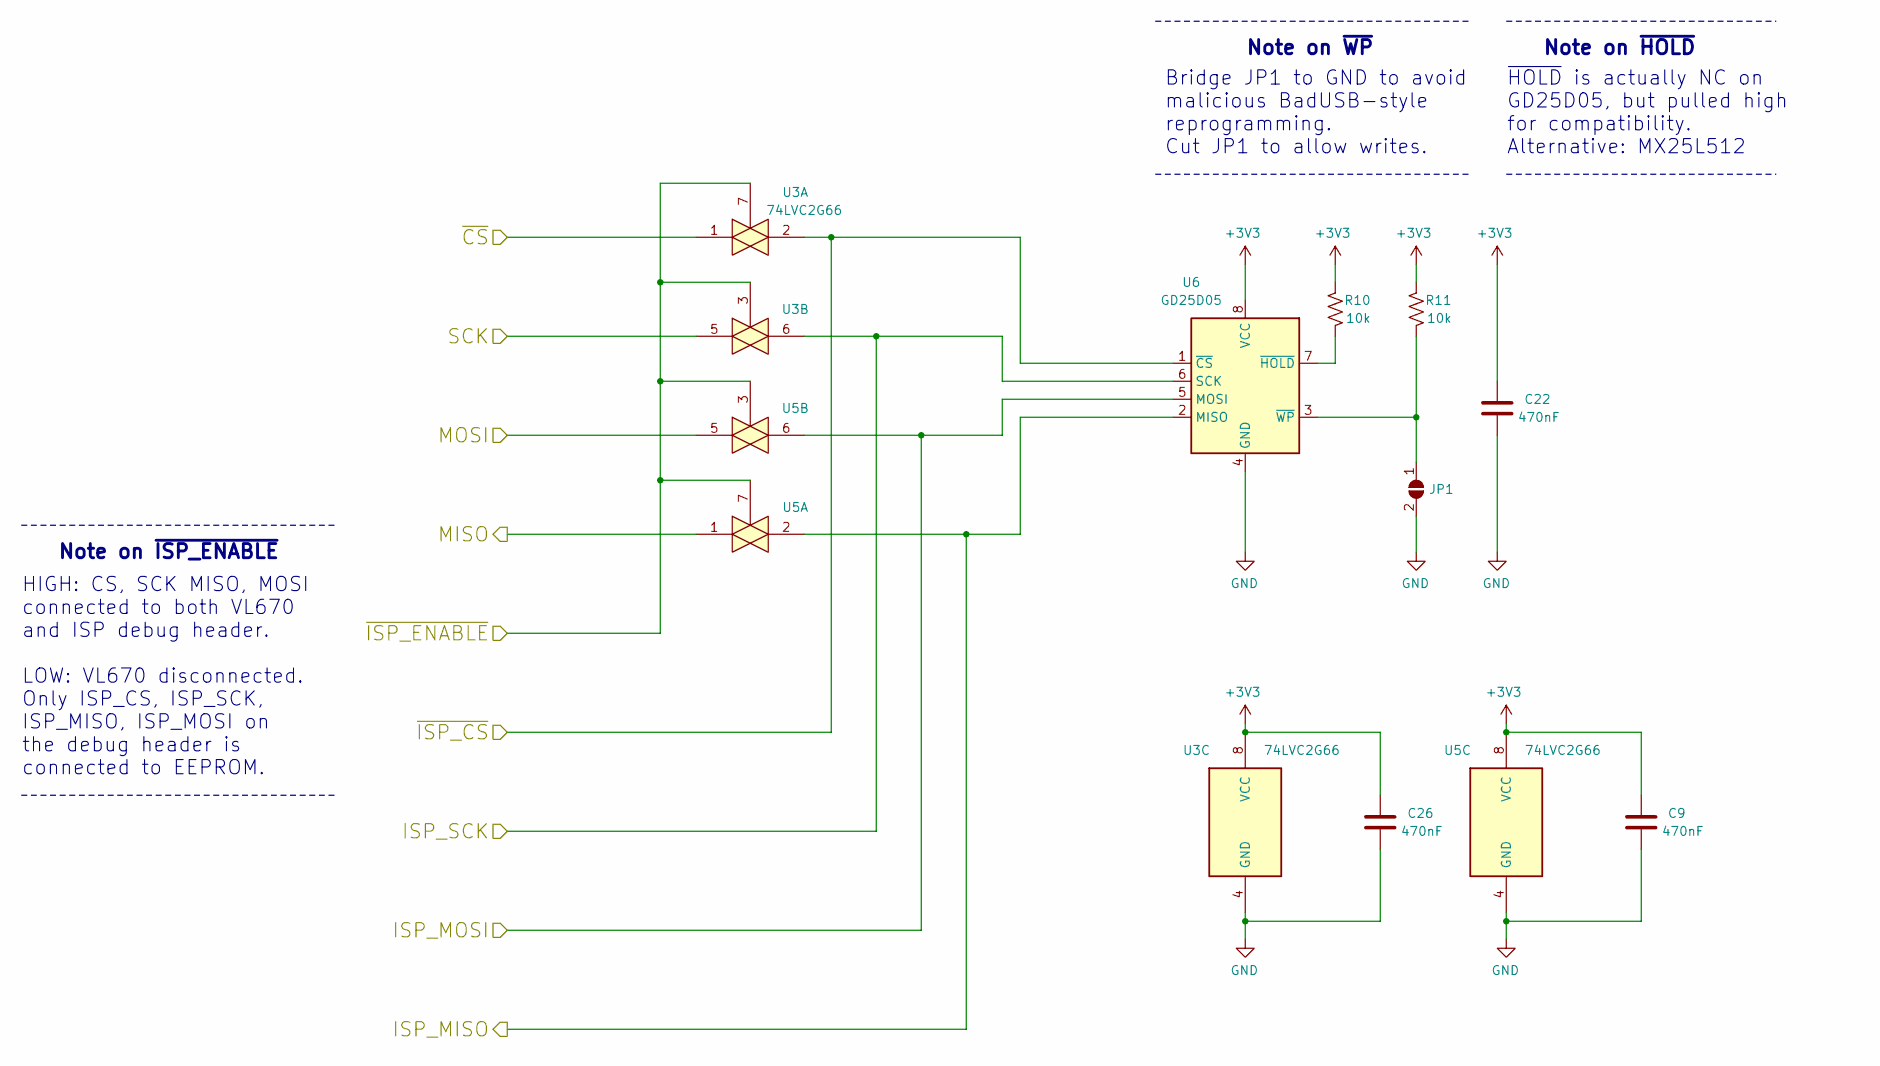
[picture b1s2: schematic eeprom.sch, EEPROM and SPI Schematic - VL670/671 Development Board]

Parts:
C9, C22, C26: 470nF; C_0603_1608Metric_Pad1.08x0.95mm_HandSolder
JP1: SolderJumper_2_Open; SolderJumper-2_P1.3mm_Open_RoundedPad1.0x1.5mm
R10, R11: 10k; R_0603_1608Metric_Pad0.98x0.95mm_HandSolder
U3, U5: 74LVC2G66; VSSOP-8_2.4x2.1mm_P0.5mm
U6: GD25D05; SOIC-8_3.9x4.9mm_P1.27mm

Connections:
+3V3: C9.1, C22.1, C26.1, R10.1, R11.1, U3.8 (VCC), U5.8 (VCC), U6.8 (VCC); also elsewhere on the board
/eeprom/ISP_MISO: U5.2, U6.2 (MISO); also elsewhere on the board
/eeprom/ISP_MOSI: U5.6, U6.5 (MOSI); also elsewhere on the board
/eeprom/ISP_SCK: U3.6, U6.6 (SCK); also elsewhere on the board
/eeprom/MISO: U5.1; also elsewhere on the board
/eeprom/MOSI: U5.5; also elsewhere on the board
/eeprom/SCK: U3.5; also elsewhere on the board
/eeprom/~CS: U3.1; also elsewhere on the board
/eeprom/~ISP_CS: U3.2, U6.1 (~CS); also elsewhere on the board
GND: C9.2, C22.2, C26.2, JP1.2 (B), U3.4 (GND), U5.4 (GND), U6.4 (GND); also elsewhere on the board
unnamed: JP1.1 (A), R11.2, U6.3 (~WP)
unnamed: R10.2, U6.7 (~HOLD)
~EXT_RESET: U3.3, U3.7, U5.3, U5.7; also elsewhere on the board

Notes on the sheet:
HIGH: CS, SCK MISO, MOSI connected to both VL670 and ISP debug header. LOW: VL670 disconnected. Only ISP_CS, ISP_SCK, ISP_MISO, ISP_MOSI on the debug header is connected to EEPROM.
Note on ~ISP_ENABLE
Bridge JP1 to GND to avoid malicious BadUSB-style reprogramming. Cut JP1 to allow writes.
Note on ~WP
Note on ~HOLD
~HOLD~ is actually NC on GD25D05, but pulled high for compatibility. Alternative: MX25L512

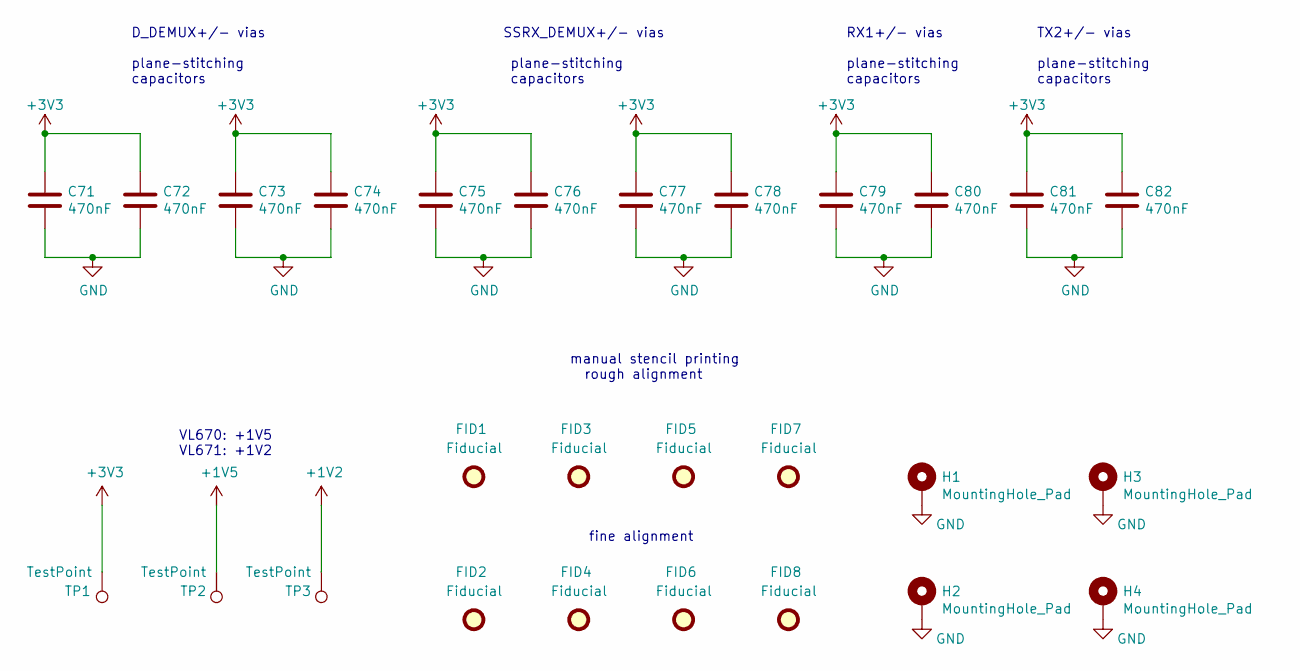
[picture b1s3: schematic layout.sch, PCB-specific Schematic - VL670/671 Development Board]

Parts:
C71, C72, C73, C74, C75, C76, C77, C78, C79, C80, C81, C82: 470nF; C_0402_1005Metric_Pad0.74x0.62mm_HandSolder
FID1, FID3, FID5, FID7: Fiducial; StencilFiducial_1mm
FID2, FID4, FID6, FID8: Fiducial; StencilFiducial_0.5mm
H1, H2, H3, H4: MountingHole_Pad; MountingHole_2.5mm_Pad_Via
TP1, TP2, TP3: TestPoint; TestPoint_Pad_D1.0mm

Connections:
+1V2: TP3.1; also elsewhere on the board
+1V5: TP2.1; also elsewhere on the board
+3V3: C71.1, C72.1, C73.1, C74.1, C75.1, C76.1, C77.1, C78.1, C79.1, C80.1, C81.1, C82.1, TP1.1; also elsewhere on the board
GND: C71.2, C72.2, C73.2, C74.2, C75.2, C76.2, C77.2, C78.2, C79.2, C80.2, C81.2, C82.2, H1.1, H2.1, H3.1, H4.1; also elsewhere on the board

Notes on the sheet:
D_DEMUX+/- vias plane-stitching capacitors
RX1+/- vias plane-stitching capacitors
SSRX_DEMUX+/- vias plane-stitching capacitors
TX2+/- vias plane-stitching capacitors
fine alignment
manual stencil printing rough alignment
VL670: +1V5 VL671: +1V2

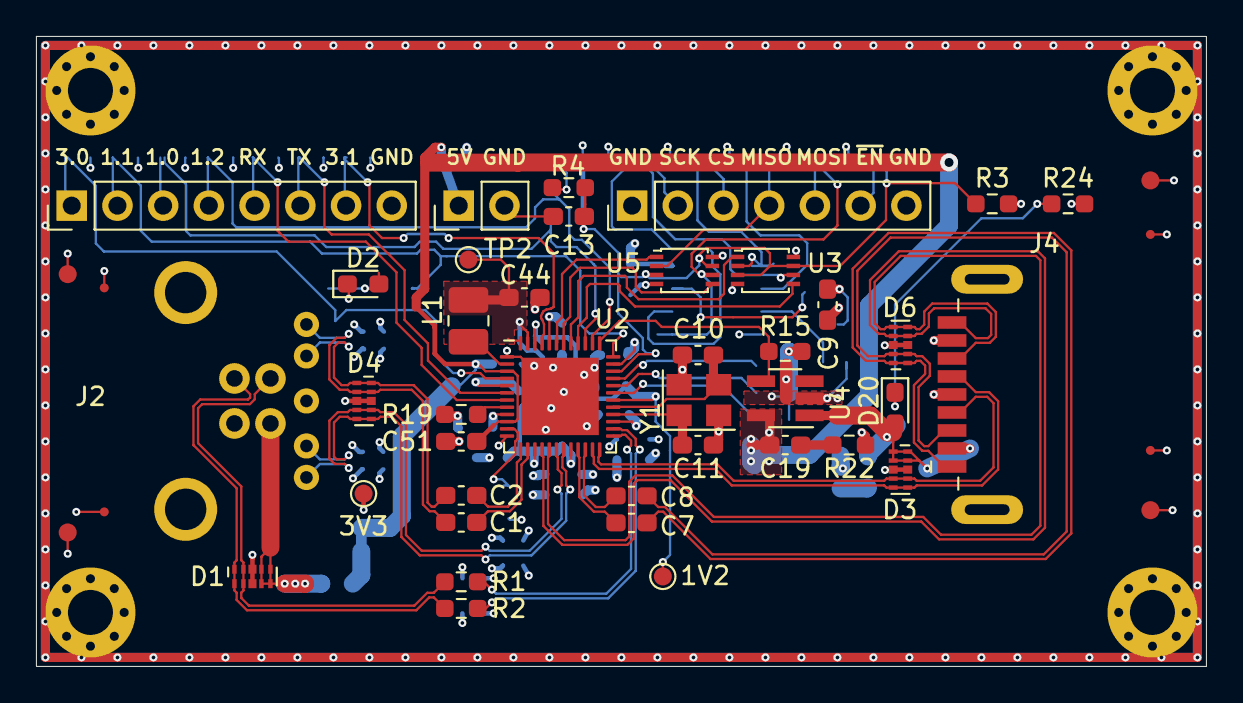
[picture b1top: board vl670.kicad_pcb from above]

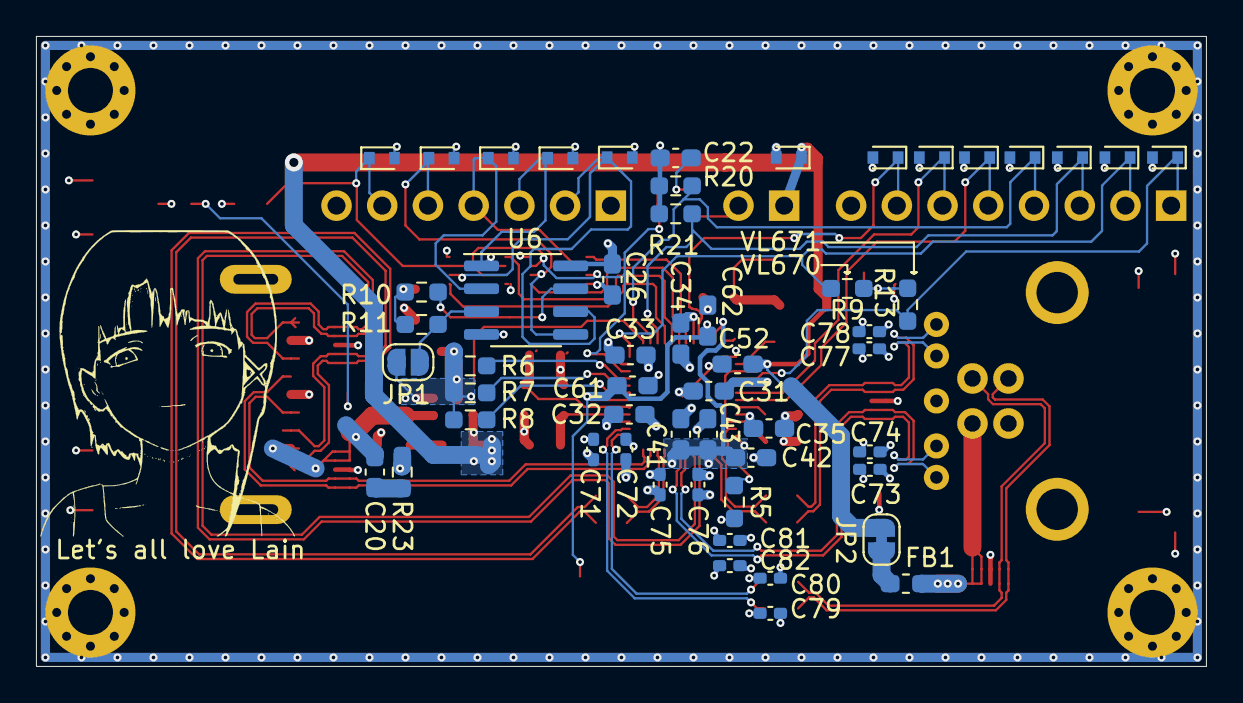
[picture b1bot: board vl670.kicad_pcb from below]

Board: 4 copper layers, 65.0 x 35.0 mm, 105 parts (54 on the bottom side), 57 nets.

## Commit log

2021-04-09 initial commit.
2021-06-18 First private release.
2021-06-18 Change R13 to a no-connection item
2021-06-18 Change GPIO connections to match firmware.
2021-06-29 various changes for v0.01 public release.
2021-06-29 README.md: add README.
2021-06-29 COPYING: add CC0 license.
2021-06-29 gerber: add gerber files.
2021-06-29 README.md: describe PCB stack-up.
2021-06-29 vl670-schematics.pdf: add PDF schematics.
2021-06-29 vl670-layout.pdf: add layout.
2021-06-29 rename components and footprints.
2021-06-29 add photos
2021-06-29 README.md: fix typo
2021-06-30 README.md: document more bugs.
2021-06-30 README.md: change "author" to "designer".
2021-06-30 README.md: move the position of photos
2021-06-30 README.md: add schematics links
2021-06-30 README.md: add firmware documentation.
2021-06-30 README.md: fix "GitHub" typo.
2021-06-30 README.md: clarify the OEM hardware behavior
2021-06-30 README.md: copyedit
2021-06-30 README.md: more copyedits.
2021-06-30 README.md: more typo fixes
2021-06-30 README.md: change schematic links to "raw"
2021-06-30 README.md: add datasheet links
2021-06-30 README.md: fix datasheet link.
2021-06-30 README.md: remove the redundant word "download".
2021-07-01 README.md: describe /EN and /RESET connection.
2021-07-01 vl670-schematics.pdf: use machine-readable PDF, not raster.
2021-07-02 README.md: more information on voltage level and debug headers.
2021-07-04 README.md: power and signal integrity.
2021-07-04 README.md: typo
2021-07-04 README.md: adjust power integrity description.
2021-07-06 README.md: quartz crystal loading capacitance bug.
2021-07-06 README.md: add information about VL671 compatibility.
2021-07-08 README.md: update on the crystal frequency bug.
2021-07-08 README.md: more information on crystal.
2021-07-09 bom/README.md: add BOM draft.
2021-07-09 README.md: add BOM link.
2021-07-10 bom/README.md: fix incorrect capacitor numbers.
2021-07-10 README.md: update for VL671 firmware information.
2021-07-26 README.md: update on inrush current.
2021-08-12 vl670.sch: change crystal and loading capacitance
2021-08-12 README.md: crystal issue solved.
2021-08-12 bom/README.md: update BOM for XTAL and capacitors.
2021-08-12 README.md: 5 V inrush problem solved.
2021-08-12 README.md: USB 3 passthrough update.
2021-08-12 README.md: renumber bugs.
2021-08-12 vl670.sch: change downstream capacitance value to 220 uF.
2021-08-12 bom/README.md: remove 100 uF, more 220 uF
2021-08-12 schematics/vl670-schematics.pdf: regenerate schematics.
2021-10-25 README.md: fix serious typos in inrush description.
2021-10-26 README.md, photos: update for v0.02.
2021-10-26 v0.02.
2021-10-26 schematics: update schematics and layouts.
2021-10-26 bom: update BOM
2021-10-26 README.md: add version history.
2021-10-26 README.md: add HD3SS3220 DC biasing information.
2021-10-26 gerber: update gerber
2021-10-27 fp-info-cache: needed for fresh KiCad installs.
2021-10-27 vl670-cache.lib: needed for fresh KiCad installs.
2021-10-31 usb-b edition
2021-10-31 vl670.kicad_pcb: adjust copper fill
2021-10-31 vl670.kicad_pcb: adjust copper fills
2021-10-31 gerber: update gerber files
2021-10-31 vl670.kicad_pcb: final adjustments
2021-10-31 gerber: generate gerber files
2021-10-31 fix incorrect RX/TX pairs
2021-10-31 gerber: regenerate gerber
2021-11-25 misc modifications.
2021-11-25 change revision number to 0.02b
2021-11-25 README.md: update for USB Type-B design.
2021-11-25 photos: add a photo, delete outdated render.
2021-11-25 README.md: add photos.
2021-11-25 library: add missing USB-C connector footprint
2021-11-25 vl670-schematics.pdf: update schematics
2021-11-25 vl670.kicad_pcb: update fab layers
2021-11-25 vl670-layout.pdf: update layout.
2021-11-25 README.md: update links to usb-b branch.

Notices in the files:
eeprom.sch:
License: CC 0, “No Rights Reserved”
